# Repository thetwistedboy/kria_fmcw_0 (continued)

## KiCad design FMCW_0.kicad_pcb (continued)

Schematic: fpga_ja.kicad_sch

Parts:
C26: 2.2u; C_0402_1005Metric; Digikey PN 1276-1108-1-ND
C30, C32: 100n; C_0402_1005Metric; Digikey PN 1276-1043-1-ND
D4: GREEN; LED_0603_1608Metric
J1: Conn_02x07_Odd_Even; PinHeader_2x07_P2.00mm_Horizontal; Digikey PN WM9841-ND
LCD1: MSP3520; ILI9488_SPI_TFT
R39, R40, R41, R42, R44, R45, R46, R47, R48, R49, R50: 22; R_0402_1005Metric; Digikey PN 541-22.0LCT-ND
R43, R101, R102: 0; R_0402_1005Metric; Digikey PN 311-0.0JRCT-ND
R95: 470; R_0402_1005Metric; Digikey PN 311-470LRCT-ND
R99, R100: 4.7k; R_0402_1005Metric; Digikey PN 311-4.7KJRCT-ND
R103: DNI; R_0402_1005Metric
SW2: SW_Push; SW_Push_1P1T_NO_CK_KMR2; Digikey PN 108-KMR211GLFSCT-ND
SW3: SW_DIP_x04; SW_DIP_SPSTx04_Slide_Omron_A6H-4101_W6.15mm_P1.27mm; Digikey PN 39-A6H-4101-ND
U16: Kria K24 SoM; Kria_K24
U31: MCP3221; SOT-23-5

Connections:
+1V8: J1.14, U16.JA_D1 (VCCO_HPA), U16.JA_D2 (VCCO_HPA); also elsewhere on the board
+3V3: C26.1, C30.2, C32.2, LCD1.1 (VCC), R99.2, R100.2, U16.JA_B13 (VCCO_HDA), U16.JA_B14 (VCCO_HDA), U31.1 (V_{DD}); also elsewhere on the board
+5V0: U16.JA_A59 (VCC_SOM), U16.JA_A60 (VCC_SOM), U16.JA_B60 (VCC_SOM), U16.JA_C59 (VCC_SOM), U16.JA_C60 (VCC_SOM), U16.JA_D60 (VCC_SOM); also elsewhere on the board
/RFFE/rf_ps_pg: U16.JA_C15 (PS_POR_B); also elsewhere on the board
/RFFE/rffe_ps_en: R101.2, R103.1; also elsewhere on the board
/RFFE/sample_clk: U16.JA_D16 (HDA_00_CC); also elsewhere on the board
/RFFE/src_ce: U16.JA_A4 (HPA_06N); also elsewhere on the board
/RFFE/src_clk: U16.JA_A6 (HPA_CLK0P_CLK); also elsewhere on the board
/RFFE/src_data: U16.JA_B1 (HPA_05P_CC); also elsewhere on the board
/RFFE/src_le: U16.JA_A3 (HPA_06P); also elsewhere on the board
/RFFE/src_mod: U16.JA_A7 (HPA_CLK0N); also elsewhere on the board
/RFFE/src_muxout: U16.JA_B2 (HPA_05N_CC); also elsewhere on the board
/RFFE/src_trig1: U16.JA_D4 (HPA_02P); also elsewhere on the board
/RFFE/src_trig2: U16.JA_D5 (HPA_02N); also elsewhere on the board
/efuse/Imon: U31.3 (A_{IN}); also elsewhere on the board
/fpga/5V0_PG: U16.JA_B26 (PWROFF_C2M_B); also elsewhere on the board
/fpga/eth/eth_rx_clk: U16.JA_D32 (MIO44); also elsewhere on the board
/fpga/eth/eth_rx_ctrl: U16.JA_C36 (MIO49); also elsewhere on the board
/fpga/eth/eth_rx_d0: U16.JA_D33 (MIO45); also elsewhere on the board
/fpga/eth/eth_rx_d1: U16.JA_D34 (MIO46); also elsewhere on the board
/fpga/eth/eth_rx_d2: U16.JA_C34 (MIO47); also elsewhere on the board
/fpga/eth/eth_rx_d3: U16.JA_C35 (MIO48); also elsewhere on the board
/fpga/eth/eth_tx_clk: U16.JA_B32 (MIO38); also elsewhere on the board
/fpga/eth/eth_tx_ctrl: U16.JA_A36 (MIO43); also elsewhere on the board
/fpga/eth/eth_tx_d0: U16.JA_B33 (MIO39); also elsewhere on the board
/fpga/eth/eth_tx_d1: U16.JA_B34 (MIO40); also elsewhere on the board
/fpga/eth/eth_tx_d2: U16.JA_A34 (MIO41); also elsewhere on the board
/fpga/eth/eth_tx_d3: U16.JA_A35 (MIO42); also elsewhere on the board
/fpga/eth/md_mdc: U16.JA_D13 (HPA_14P); also elsewhere on the board
/fpga/eth/md_mdio: U16.JA_D14 (HPA_14N); also elsewhere on the board
/fpga/fpga_ja/PS_SRST_N: J1.2, SW2.2, U16.JA_C16 (PS_SRST_C2M_B)
/fpga/fpga_ja/PS_SUPPLY_START: R102.2, R103.2
/fpga/fpga_ja/TCK: R41.2, U16.JA_A25 (JTAG_TCK_C2M)
/fpga/fpga_ja/TDI: R39.2, U16.JA_A24 (JTAG_TDI_C2M)
/fpga/fpga_ja/TDO: R40.2, U16.JA_A23 (JTAG_TDO_M2C)
/fpga/fpga_ja/TMS: R42.2, U16.JA_A22 (JTAG_TMS_C2M)
/fpga/fpga_ja/i2c_33_scl: R99.1, U16.JA_C22 (HDA_18), U31.5 (SCL)
/fpga/fpga_ja/i2c_33_sda: R100.1, U16.JA_C23 (HDA_19), U31.4 (SDA)
/fpga/fpga_ja/tft_cs_n: R44.1, U16.JA_D22 (HDA_14)
/fpga/fpga_ja/tft_dc: R46.1, U16.JA_D20 (HDA_12)
/fpga/fpga_ja/tft_led: R49.1, U16.JA_C19 (HDA_07)
/fpga/fpga_ja/tft_miso: R50.1, U16.JA_C18 (HDA_06)
/fpga/fpga_ja/tft_mosi: R47.1, U16.JA_D18 (HDA_02)
/fpga/fpga_ja/tft_rst: R45.1, U16.JA_D21 (HDA_13)
/fpga/fpga_ja/tft_sck: R48.1, U16.JA_D17 (HDA_01)
/fpga/fpga_ja/uart_rxd: U16.JA_A43 (MIO74); also elsewhere on the board
/fpga/fpga_ja/uart_txd: U16.JA_A44 (MIO75); also elsewhere on the board
/fpga/fpga_ja/ulpi_clkout: U16.JA_D36 (MIO52); also elsewhere on the board
/fpga/fpga_ja/ulpi_d0: U16.JA_C39 (MIO56); also elsewhere on the board
/fpga/fpga_ja/ulpi_d1: U16.JA_C40 (MIO57); also elsewhere on the board
/fpga/fpga_ja/ulpi_d2: U16.JA_D38 (MIO54); also elsewhere on the board
/fpga/fpga_ja/ulpi_d3: U16.JA_B41 (MIO59); also elsewhere on the board
/fpga/fpga_ja/ulpi_d4: U16.JA_B42 (MIO60); also elsewhere on the board
/fpga/fpga_ja/ulpi_d5: U16.JA_A38 (MIO61); also elsewhere on the board
/fpga/fpga_ja/ulpi_d6: U16.JA_A39 (MIO62); also elsewhere on the board
/fpga/fpga_ja/ulpi_d7: U16.JA_A40 (MIO63); also elsewhere on the board
/fpga/fpga_ja/ulpi_dir: U16.JA_D37 (MIO53); also elsewhere on the board
/fpga/fpga_ja/ulpi_nxt: U16.JA_C38 (MIO55); also elsewhere on the board
/fpga/fpga_ja/ulpi_stp: U16.JA_B40 (MIO58); also elsewhere on the board
/fpga/fpga_ja/usb_reset: U16.JA_D40 (MIO64); also elsewhere on the board
GND: C26.2, C30.1, C32.1, D4.1 (K), J1.1, J1.3, J1.5, J1.7, J1.9, J1.11, J1.13, LCD1.2 (GND), R43.1, SW2.1, SW3.5, SW3.6, SW3.7, SW3.8, U16.JA_A2 (GND), U16.JA_A5 (GND), U16.JA_A8 (GND), U16.JA_A11 (GND), U16.JA_A14 (GND), U16.JA_A18 (GND), U16.JA_A21 (GND), U16.JA_A26 (GND), U16.JA_A33 (GND), U16.JA_A37 (GND), U16.JA_A41 (GND), U16.JA_A45 (GND), U16.JA_A46 (GND), U16.JA_A49 (GND), U16.JA_A50 (GND), U16.JA_A53 (GND), U16.JA_A54 (GND), U16.JA_A57 (GND), U16.JA_A58 (GND), U16.JA_B3 (GND), U16.JA_B6 (GND), U16.JA_B9 (GND), U16.JA_B12 (GND), U16.JA_B15 (GND), U16.JA_B19 (GND), U16.JA_B23 (GND), U16.JA_B27 (GND), U16.JA_B31 (GND), U16.JA_B35 (GND), U16.JA_B39 (GND), U16.JA_B43 (GND), U16.JA_B47 (GND), U16.JA_B48 (GND), U16.JA_B51 (GND), U16.JA_B52 (GND), U16.JA_B55 (GND), U16.JA_B56 (GND), U16.JA_B59 (GND), U16.JA_C1 (GND), U16.JA_C2 (GND), U16.JA_C5 (GND), U16.JA_C8 (GND), U16.JA_C11 (GND), U16.JA_C14 (GND), U16.JA_C17 (GND), U16.JA_C21 (GND), U16.JA_C25 (GND), U16.JA_C29 (GND), U16.JA_C33 (GND), U16.JA_C37 (GND), U16.JA_C41 (GND), U16.JA_C46 (GND), U16.JA_C49 (GND), U16.JA_C50 (GND), U16.JA_C53 (GND), U16.JA_C54 (GND), U16.JA_C57 (GND), U16.JA_C58 (GND), U16.JA_D3 (GND), U16.JA_D6 (GND), U16.JA_D9 (GND), U16.JA_D12 (GND), U16.JA_D15 (GND), U16.JA_D19 (GND), U16.JA_D23 (GND), U16.JA_D27 (GND), U16.JA_D31 (GND), U16.JA_D35 (GND), U16.JA_D39 (GND), U16.JA_D43 (GND), U16.JA_D47 (GND), U16.JA_D48 (GND), U16.JA_D51 (GND), U16.JA_D52 (GND), U16.JA_D55 (GND), U16.JA_D56 (GND), U16.JA_D59 (GND), U31.2 (V_{SS}); also elsewhere on the board
unnamed: D4.2 (A), R95.1
unnamed: J1.6, R39.1
unnamed: J1.8, R40.1
unnamed: J1.10, R41.1
unnamed: J1.12, R42.1
unnamed: LCD1.3 (CS), R44.2
unnamed: LCD1.5 (DC), R46.2
unnamed: LCD1.8 (LED), R49.2
unnamed: LCD1.4 (RST), R45.2
unnamed: LCD1.7 (SCK), R48.2
unnamed: LCD1.6 (SDI), R47.2
unnamed: LCD1.9 (SDO), R50.2
unnamed: R95.2, U16.JA_B16 (HDA_03)
unnamed: SW3.1, U16.JA_A27 (MODE0_C2M)
unnamed: SW3.2, U16.JA_A28 (MODE1_C2M)
unnamed: SW3.3, U16.JA_A29 (MODE2_C2M)
unnamed: SW3.4, U16.JA_A30 (MODE3_C2M)
unnamed: R101.1, U16.JA_A20 (VCCOEN_PL_M2C)
unnamed: R102.1, U16.JA_A19 (VCCOEN_PS_M2C)
unnamed: R43.2, U16.JA_A1 (VCC_BATT)

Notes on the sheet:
HPIO
MDIO MIO50-51
USB0 MIO52-63
GEM1 MIO38-49

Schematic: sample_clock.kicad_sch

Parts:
C1, C2: 100n; C_0402_1005Metric; Digikey PN 1276-1043-1-ND
FB1: FerriteBead_Small; R_0402_1005Metric; Digikey PN 490-5203-1-ND
R1, R3, R4: 10k; R_0402_1005Metric; Digikey PN RMCF0402FT10K0CT-ND
R2, R6, R7: 22; R_0402_1005Metric; Digikey PN 541-22.0LCT-ND
R5, R8: 49.9; R_0402_1005Metric; Digikey PN P49.9LCT-ND
U3: LMK1C1103A; TSSOP-8_4.4x3mm_P0.65mm
Y1: ECS-2520MV-160-BN; Oscillator_SMD_ECS_2520MV-xxx-xx-4Pin_2.5x2.0mm

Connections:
+3V3: C2.1, FB1.1, R4.1, U3.6 (VDD); also elsewhere on the board
/RFFE/ADC/sample_clk: R8.2; also elsewhere on the board
/RFFE/sample_clk: R6.2; also elsewhere on the board
/RFFE/sample_clk_out: R7.2; also elsewhere on the board
/RFFE/sample_clock/clk0: R5.2; also elsewhere on the board
GND: C1.2, C2.2, R3.2, U3.4 (GND), Y1.2 (GND); also elsewhere on the board
unnamed: R4.2, U3.2 (1G)
unnamed: R2.2, R3.1, U3.1 (CLKIN)
unnamed: R5.1, U3.3 (Y0)
unnamed: R6.1, U3.8 (Y1)
unnamed: R7.1, U3.5 (Y2)
unnamed: R8.1, U3.7 (Y3)
unnamed: R2.1, Y1.3 (OUT)
unnamed: R1.1, Y1.1 (Tri-State)
unnamed: C1.1, FB1.2, R1.2, Y1.4 (VDD)

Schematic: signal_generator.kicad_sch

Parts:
C18, C19, C22, C23, C25, C28, C31, C34: 100n; C_0402_1005Metric; Digikey PN 1276-1043-1-ND
C20: 1u; C_0402_1005Metric; Digikey PN 1276-1067-1-ND
C21: 10n; C_0402_1005Metric; Digikey PN 490-1313-2-ND
C24, C27: C_Small; C_0402_1005Metric
C29, C33: 220p; C_0402_1005Metric; Digikey PN 490-1293-1-ND
R16, R17, R20: 49.9; R_0402_1005Metric; Digikey PN P49.9LCT-ND
R18, R19: 10k; R_0402_1005Metric; Digikey PN RMCF0402FT10K0CT-ND
R21: R_Small; R_0402_1005Metric
R22, R23: 18; R_0402_1005Metric; Digikey PN CR0402-FX-18R0GLFCT-ND
R24: 68; R_0402_1005Metric; Digikey PN P68.0LCT-ND
R25: 43; R_0402_1005Metric; Digikey PN 311-43JRCT-ND
R26, R27, R28: 22; R_0402_1005Metric; Digikey PN 541-22.0LCT-ND
RN3, RN4: 22; R_Array_Convex_4x0402
U10: LMX2491; QFN-24-1EP_4x4mm_P0.5mm_EP2.6x2.6mm
U11: MAX275X; MSOP-8_3x3mm_P0.65mm

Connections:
+3.3VA: C20.1, C21.1, C22.1, C25.1, C29.1, C33.1, R18.1, U10.6 (Vcc), U10.7 (Vcc), U10.8 (Vcc), U10.18 (Vcc), U10.19 (Vcc), U10.22 (Vcp), U11.4 (~SHDN), U11.5 (VCC1), U11.6 (VCC2); also elsewhere on the board
/RFFE/demodulator/LO: R28.2; also elsewhere on the board
/RFFE/sample_clock/clk0: R16.1; also elsewhere on the board
/RFFE/signal_generator/f_out1: R27.2; also elsewhere on the board
/RFFE/src_ce: RN3.7 (R2.2); also elsewhere on the board
/RFFE/src_clk: RN3.6 (R3.2); also elsewhere on the board
/RFFE/src_data: RN4.5 (R4.2); also elsewhere on the board
/RFFE/src_le: RN3.8 (R1.2); also elsewhere on the board
/RFFE/src_mod: RN3.5 (R4.2); also elsewhere on the board
/RFFE/src_muxout: RN4.6 (R3.2); also elsewhere on the board
/RFFE/src_trig1: RN4.7 (R2.2); also elsewhere on the board
/RFFE/src_trig2: RN4.8 (R1.2); also elsewhere on the board
GND: C20.2, C21.2, C22.2, C24.2, C25.2, C29.2, C31.2, C33.2, C34.2, R17.1, R19.2, R20.2, R21.2, R24.2, U10.1 (GND), U10.2 (GND), U10.3 (GND), U10.11 (GND), U10.25 (EP), U11.3 (GND), U11.8 (GND); also elsewhere on the board
unnamed: C18.1, R16.2
unnamed: C19.1, R17.2
unnamed: C23.2, R20.1
unnamed: C27.2, R21.1
unnamed: C28.2, R23.1
unnamed: R23.2, R24.1, R25.1
unnamed: R25.2, R26.2, R27.1, R28.1
unnamed: RN3.1 (R1.1), U10.15 (DATA)
unnamed: RN3.2 (R2.1), U10.14 (CLK)
unnamed: R19.1, RN3.3 (R3.1), U10.13 (CE)
unnamed: RN3.4 (R4.1), U10.12 (MOD)
unnamed: RN4.1 (R1.1), U10.21 (TRIG2)
unnamed: RN4.2 (R2.1), U10.20 (TRIG1)
unnamed: RN4.3 (R3.1), U10.17 (MUXOUT)
unnamed: R18.2, RN4.4 (R4.1), U10.16 (LE)
unnamed: C24.1, C27.1, R22.1, U10.24 (CPout)
unnamed: C28.1, U10.5 (Fin_n)
unnamed: C23.1, U10.4 (Fin_p)
unnamed: C19.2, U10.10 (OSCin_n)
unnamed: C18.2, U10.9 (OSCin_p)
unnamed: C34.1, U11.1 (BYP)
unnamed: R26.1, U11.7 (OUT)
unnamed: C31.1, R22.2, U11.2 (TUNE)

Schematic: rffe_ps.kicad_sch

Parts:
C3, C4, C7, C8: 1u; C_0402_1005Metric; Digikey PN 1276-1067-1-ND
C5, C6: 22u; C_0805_2012Metric; Digikey PN 1276-6786-1-ND
C9, C10: 2.2u; C_0402_1005Metric; Digikey PN 1276-1108-1-ND
C11, C12: 100n; C_0402_1005Metric; Digikey PN 1276-1043-1-ND
FB2, FB3: FerriteBead_Small; R_0402_1005Metric; Digikey PN 490-5203-1-ND
L1: 4.7u; L_Wuerth_MAPI-4020; Digikey PN 732-11316-1-ND
R9, R12: 10k; R_0402_1005Metric; Digikey PN RMCF0402FT10K0CT-ND
R10: 22; R_0402_1005Metric; Digikey PN 541-22.0LCT-ND
R11: 59k; R_0402_1005Metric; Digikey PN 311-59KLRCT-ND
U4: AP63200WU; TSOT-23-6
U5: TLV76750QWDRBxQ1; VSON-8-1EP_3x3mm_P0.65mm_EP1.65x2.4mm
U6: TLV76733QWDRBxQ1; VSON-8-1EP_3x3mm_P0.65mm_EP1.65x2.4mm
U7: TPS3839K50DBZR; SOT-23; Digikey PN 296-35472-1-ND
U8: TPS3839K33DBZR; SOT-23; Digikey PN 296-35471-1-ND

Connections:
+3.3VA: FB3.2; also elsewhere on the board
+5VA: FB2.2; also elsewhere on the board
/RFFE/Vin: C3.1, U4.3 (IN); also elsewhere on the board
/RFFE/rf_ps_pg: U7.2 (~RESET), U8.2 (~RESET); also elsewhere on the board
/RFFE/rffe_ps_en: R9.2, R10.1; also elsewhere on the board
GND: C3.2, C5.1, C6.1, C7.2, C8.2, C9.2, C10.2, C11.1, C12.1, R9.1, R12.1, U4.4 (GND), U5.4 (GND), U5.6 (GND), U5.9 (PAD), U6.4 (GND), U6.6 (GND), U6.9 (PAD), U7.1 (GND), U8.1 (GND); also elsewhere on the board
unnamed: C4.1, U4.6 (BST)
unnamed: R10.2, U4.2 (EN)
unnamed: R11.2, R12.2, U4.1 (FB)
unnamed: C4.2, L1.1, U4.5 (SW)
unnamed: C5.2, C6.2, C7.1, C8.1, L1.2, R11.1, U5.5 (EN), U5.8 (IN), U6.5 (EN), U6.8 (IN)
unnamed: C10.1, C11.2, FB2.1, U5.1 (OUT), U5.3 (SNS), U7.3 (VDD)
unnamed: C9.1, C12.2, FB3.1, U6.1 (OUT), U6.3 (SNS), U8.3 (VDD)

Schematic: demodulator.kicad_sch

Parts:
C35, C36, C37: 100n; C_0402_1005Metric; Digikey PN 1276-1043-1-ND
C38, C39, C40, C41, C42, C43, C44: 100p; C_0402_1005Metric; Digikey PN 1292-1637-1-ND
C45, C46, C47, C48: 10u; C_0603_1608Metric; Digikey PN 490-7202-1-ND
C49, C50: 82p; C_0402_1005Metric; Digikey PN 490-7310-1-ND
C51, C52: 360p; C_0402_1005Metric; Digikey PN 399-14907-1-ND
C53, C54: 430p; C_0402_1005Metric; Digikey PN 490-GCM1555C1H431JA16DCT-ND
L2, L3, L4, L5: 310n; L_0402_1005Metric; Digikey PN 445-6324-1-ND
L6, L7, L8, L9: 550n; L_0402_1005Metric; Digikey PN 587-6432-1-ND
R29, R30: DNI; R_0402_1005Metric
R31: 10k; R_0402_1005Metric; Digikey PN RMCF0402FT10K0CT-ND
R32: 1.5k; R_0402_1005Metric; Digikey PN P1.50KLCT-ND
R33, R34: 499; R_0402_1005Metric; Digikey PN P499LCT-ND
U12, U13: 5400BL15B050; Balun_Johanson_5400BL15B050E
U14: ADL5380; LFCSP-24-1EP_4x4mm_P0.5mm_EP2.3x2.3mm

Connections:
+5VA: C35.2, C36.2, C37.2, C40.2, C41.2, C42.2, R32.1, U14.6 (VCC1), U14.13 (VCC2), U14.24 (VCC3); also elsewhere on the board
/RFFE/ADC/ADCI_N: C53.1, L6.2, R33.1; also elsewhere on the board
/RFFE/ADC/ADCI_P: C53.2, L7.2, R33.2; also elsewhere on the board
/RFFE/ADC/ADCQ_N: C54.2, L9.2, R34.2; also elsewhere on the board
/RFFE/ADC/ADCQ_P: C54.1, L8.2, R34.1; also elsewhere on the board
/RFFE/demodulator/LO: U12.1; also elsewhere on the board
/RFFE/demodulator/RF_in: U13.1; also elsewhere on the board
GND: C35.1, C36.1, C37.1, C40.1, C41.1, C42.1, R29.2, R30.2, R31.2, U12.2 (GND), U12.5 (GND), U13.2 (GND), U13.5 (GND), U14.1 (GND), U14.2 (GND), U14.5 (GND), U14.8 (GND), U14.11 (GND), U14.14 (GND), U14.17 (GND), U14.18 (GND), U14.20 (GND), U14.23 (GND), U14.25 (EP); also elsewhere on the board
unnamed: C38.1, U12.3
unnamed: C39.1, U12.4
unnamed: C43.1, R29.1, U13.3
unnamed: C44.1, R30.1, U13.4
unnamed: C45.2, C49.1, L2.1
unnamed: C46.2, C49.2, L3.1
unnamed: C47.2, C50.1, L4.1
unnamed: C48.2, C50.2, L5.1
unnamed: C51.1, L2.2, L6.1
unnamed: C51.2, L3.2, L7.1
unnamed: C52.1, L4.2, L8.1
unnamed: C52.2, L5.2, L9.1
unnamed: R32.2, U14.19 (ADJ)
unnamed: R31.1, U14.7 (ENBL)
unnamed: C46.1, U14.3 (IHI)
unnamed: C45.1, U14.4 (ILO)
unnamed: C38.2, U14.10 (LOIN)
unnamed: C39.2, U14.9 (LOIP)
unnamed: C47.1, U14.16 (QHI)
unnamed: C48.1, U14.15 (QLO)
unnamed: C44.2, U14.21 (RFIN)
unnamed: C43.2, U14.22 (RFIP)

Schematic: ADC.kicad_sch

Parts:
C13, C15: 100n; C_0402_1005Metric; Digikey PN 1276-1043-1-ND
C14: 100p; C_0402_1005Metric; Digikey PN 1292-1637-1-ND
C16: 10n; C_0402_1005Metric; Digikey PN 490-1313-2-ND
C17: 1u; C_0402_1005Metric; Digikey PN 1276-1067-1-ND
FB4: FerriteBead_Small; R_0402_1005Metric; Digikey PN 490-5203-1-ND
R13, R14: 10k; R_0402_1005Metric; Digikey PN RMCF0402FT10K0CT-ND
R15: 22; R_0402_1005Metric; Digikey PN 541-22.0LCT-ND
RN1, RN2: 22; R_Array_Convex_4x0402
U9: MCP3911; UQFN-20-1EP_4x4mm_P0.5mm_EP2.8x2.8mm

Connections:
+3.3VA: FB4.1, R15.2; also elsewhere on the board
/RFFE/ADC/ADCI_N: U9.3 (CH1-); also elsewhere on the board
/RFFE/ADC/ADCI_P: U9.4 (CH1+); also elsewhere on the board
/RFFE/ADC/ADCQ_N: U9.2 (CH0-); also elsewhere on the board
/RFFE/ADC/ADCQ_P: U9.1 (CH0+); also elsewhere on the board
/RFFE/ADC/adc_dvdd: C13.1, FB4.2, R13.2, U9.19 (DVDD)
/RFFE/ADC/sample_clk: U9.12 (OSC1/CLKI); also elsewhere on the board
/RFFE/adc_cs_n: RN2.8 (R1.2); also elsewhere on the board
/RFFE/adc_dr_n: RN2.7 (R2.2); also elsewhere on the board
/RFFE/adc_mdat0: RN2.6 (R3.2); also elsewhere on the board
/RFFE/adc_mdat1: RN2.5 (R4.2); also elsewhere on the board
/RFFE/adc_reset_n: RN1.8 (R1.2); also elsewhere on the board
/RFFE/adc_sck: RN1.5 (R4.2); also elsewhere on the board
/RFFE/adc_sdi: RN1.7 (R2.2); also elsewhere on the board
/RFFE/adc_sdo: RN1.6 (R3.2); also elsewhere on the board
GND: C13.2, C14.2, C15.2, C16.2, C17.2, R14.1, U9.5 (AGND), U9.7 (REFIN-), U9.8 (DGND), U9.21 (EP); also elsewhere on the board
unnamed: R14.2, RN1.1 (R1.1), U9.18 (~RESET)
unnamed: RN1.2 (R2.1), U9.17 (SDI)
unnamed: RN1.3 (R3.1), U9.16 (SDO)
unnamed: RN1.4 (R4.1), U9.15 (SCK)
unnamed: R13.1, RN2.1 (R1.1), U9.14 (~CS)
unnamed: RN2.2 (R2.1), U9.11 (~DR)
unnamed: RN2.3 (R3.1), U9.10 (MDAT0)
unnamed: RN2.4 (R4.1), U9.9 (MDAT1)
unnamed: C14.1, C16.1, C17.1, R15.1, U9.20 (AVDD)
unnamed: C15.1, U9.6 (REFIN+/OUT)

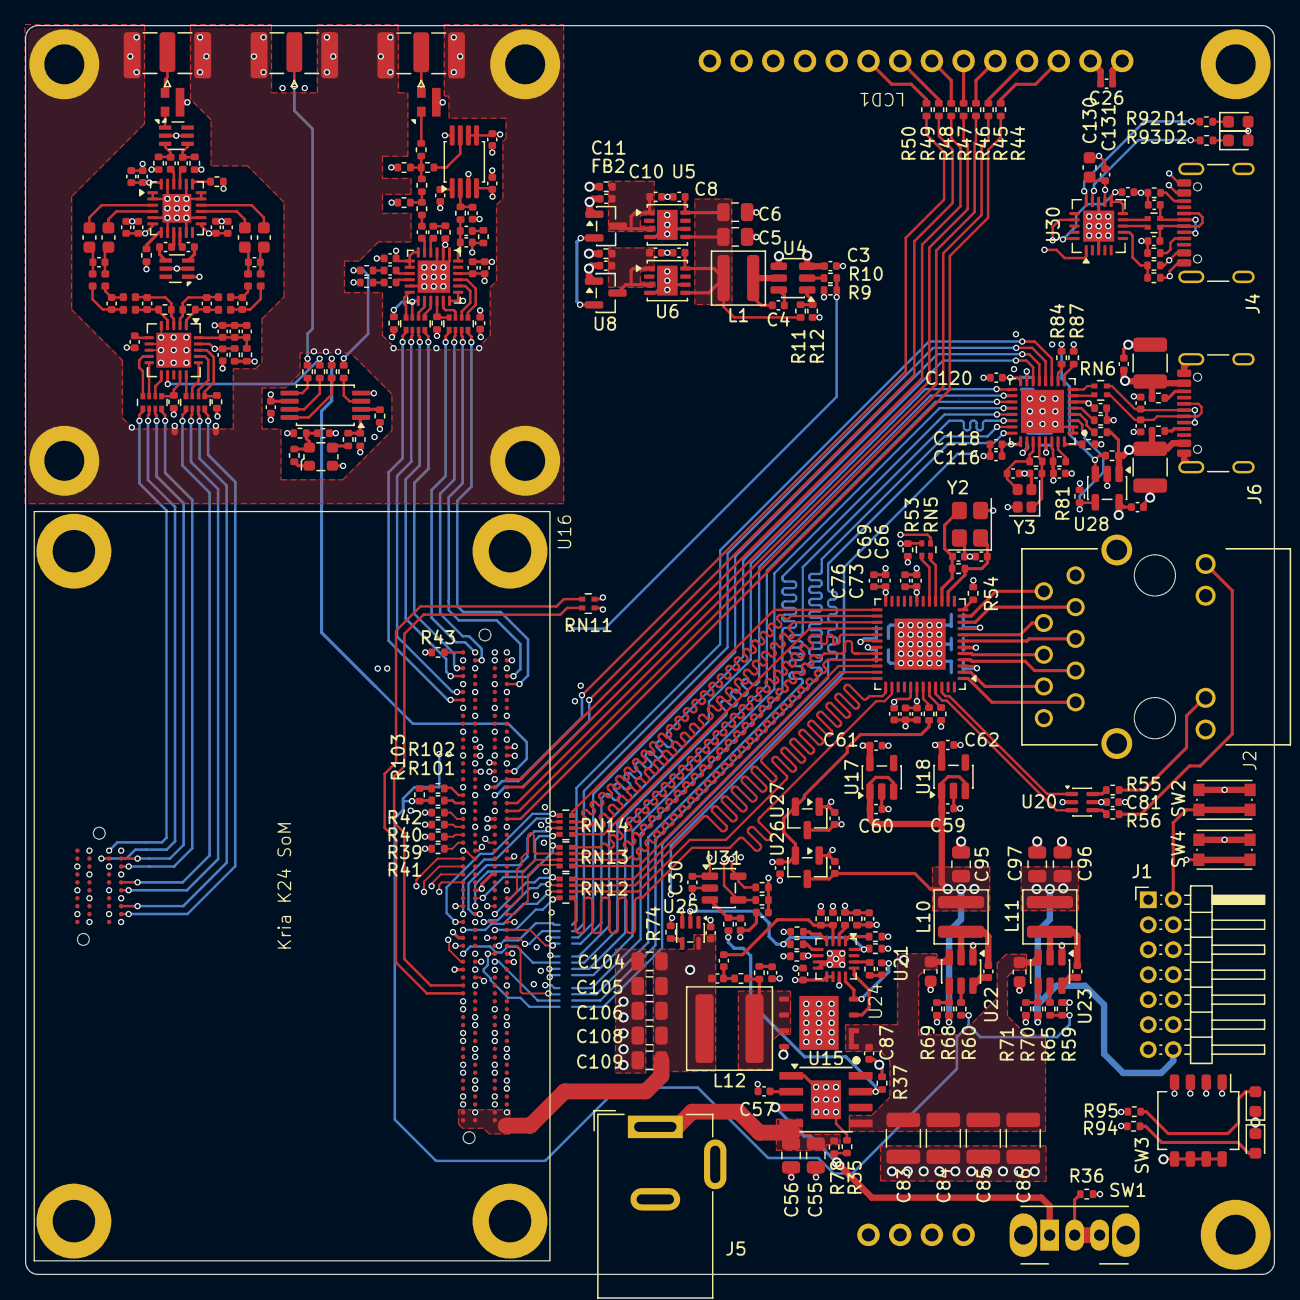
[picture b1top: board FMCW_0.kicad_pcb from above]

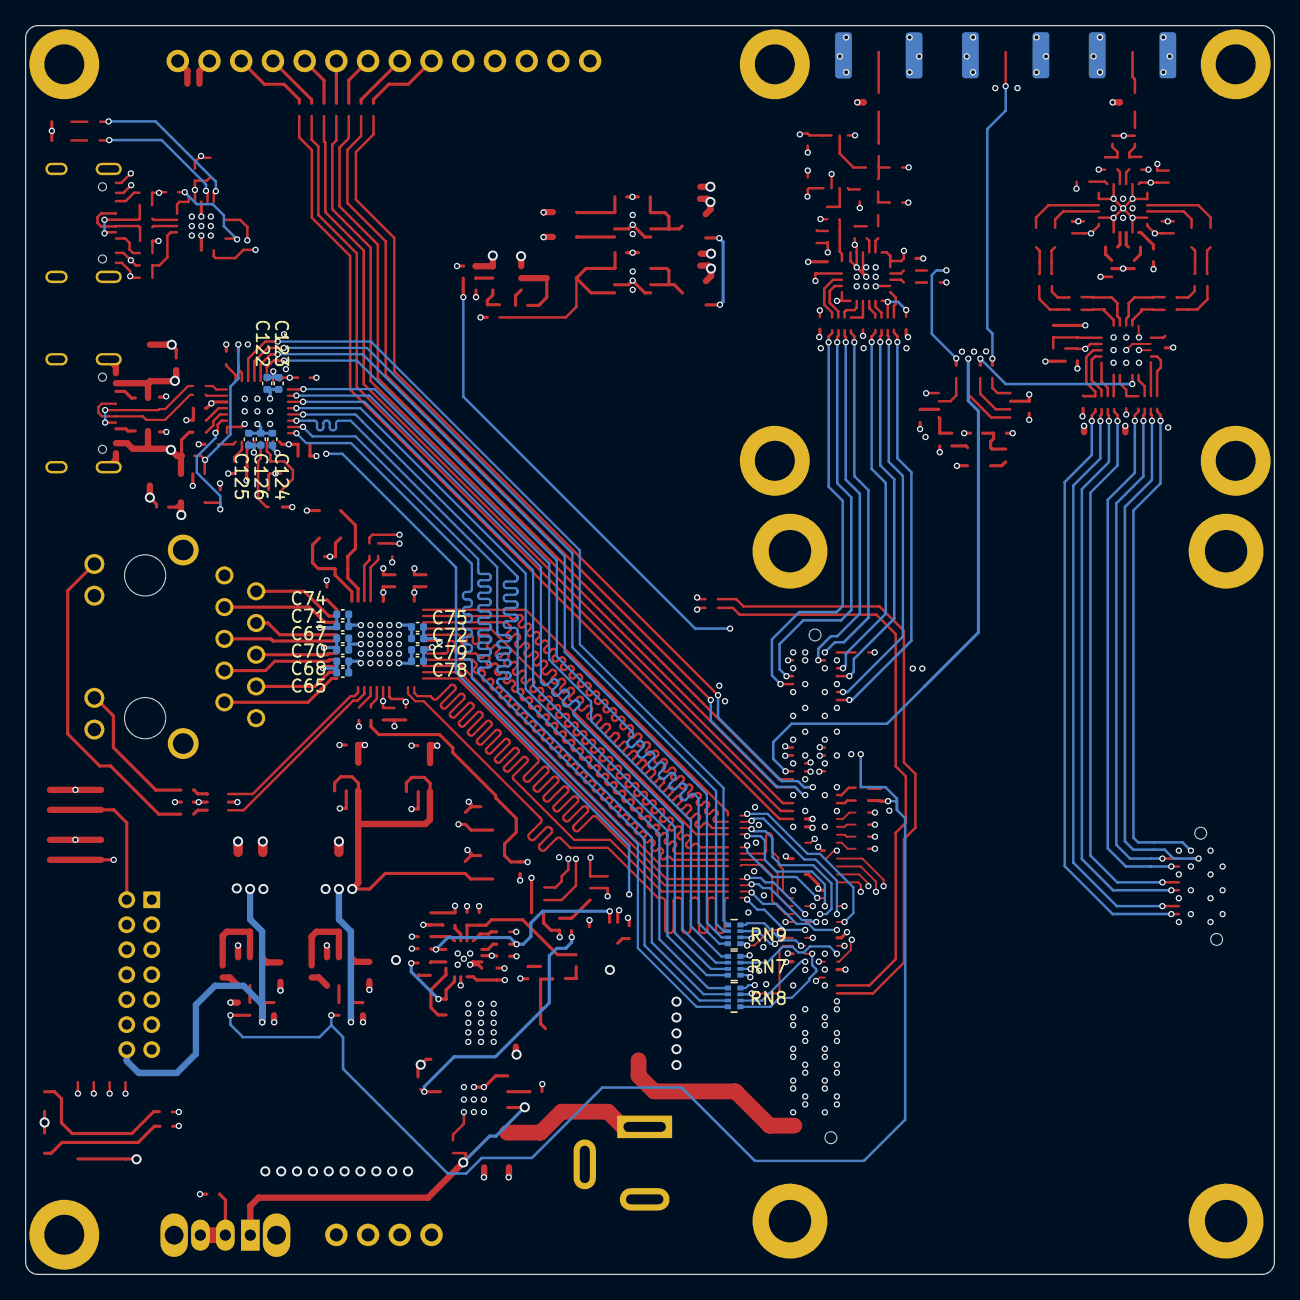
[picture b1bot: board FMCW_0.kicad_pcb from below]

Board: 6 copper layers, 100.0 x 100.0 mm, 321 parts (18 on the bottom side), 288 nets.
